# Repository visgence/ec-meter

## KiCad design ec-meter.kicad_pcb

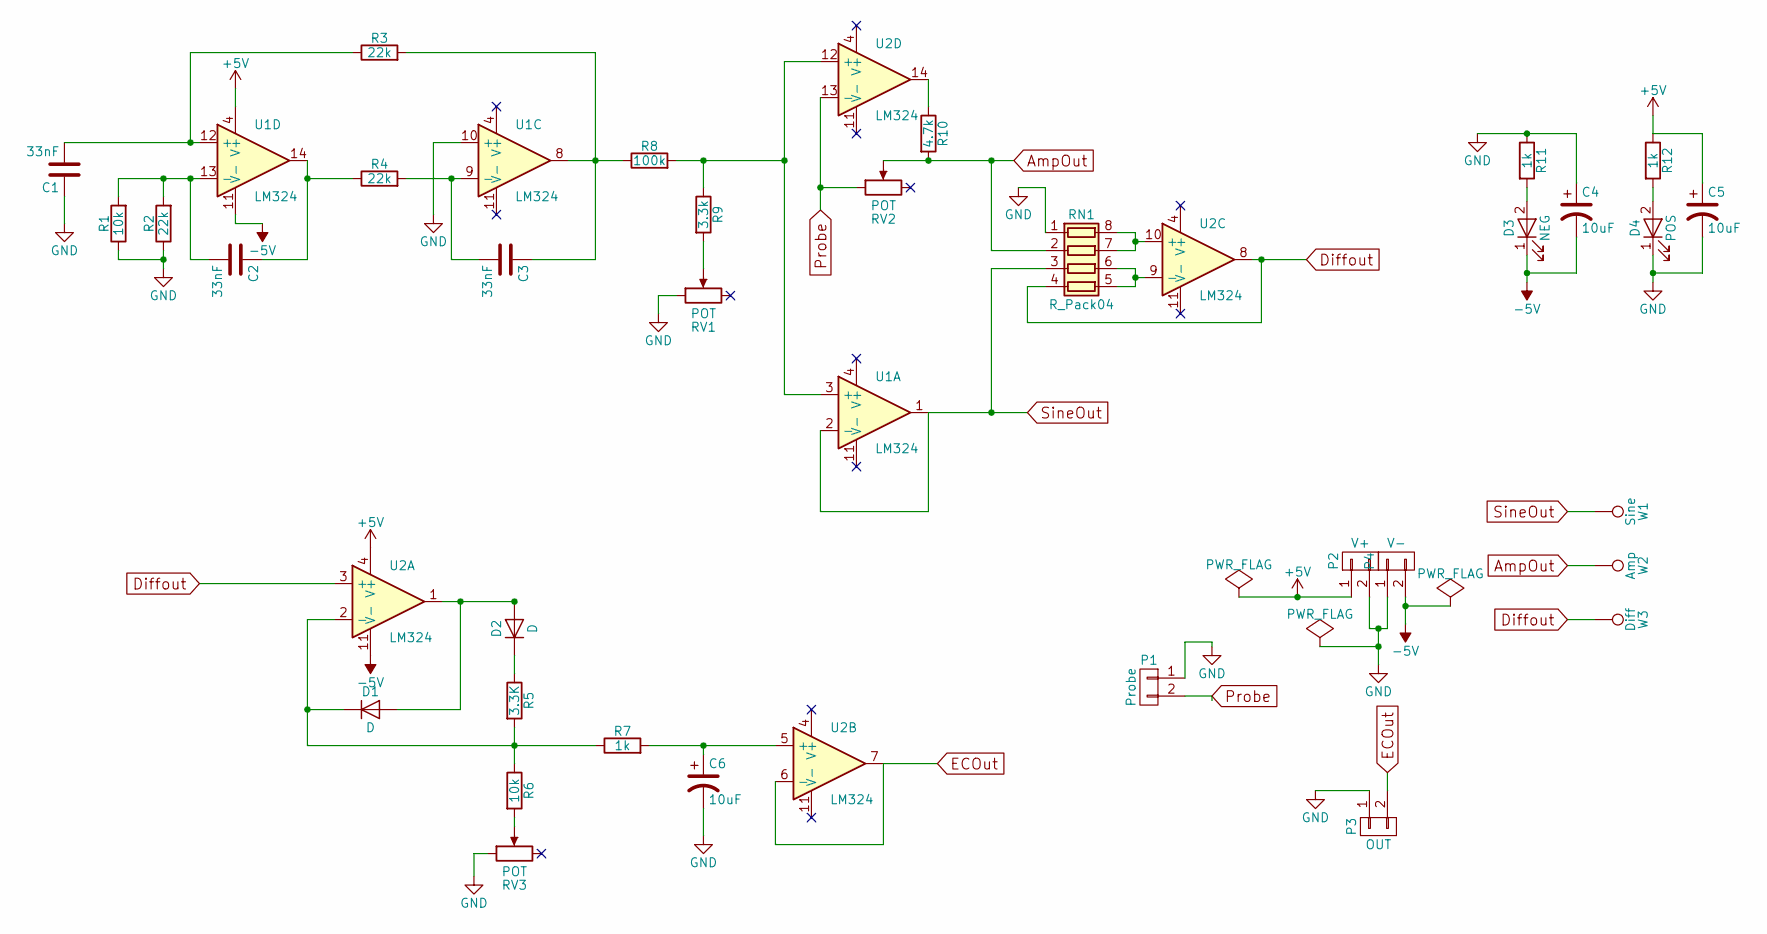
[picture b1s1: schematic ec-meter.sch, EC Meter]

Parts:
C1, C2, C3: 33nF; SM1206_VIS
C4, C5, C6: 10uF; SM1206POL_VIS
D1, D2: D; D_SOD-323
D3: NEG; LED_0603
D4: POS; LED_0603
P1: Probe; Term3.5-2
P2: V+; Term3.5-2
P3: OUT; Term3.5-2
P4: V-; Term3.5-2
R1, R6: 10k; SM0603_VIS
R2, R3, R4: 22k; SM0603_VIS
R5: 3.3K; SM0603_VIS
R7, R11, R12: 1k; SM0603_VIS
R8: 100k; SM0603_VIS
R9: 3.3k; SM0603_VIS
R10: 4.7k; SM0603_VIS
RN1: R_Pack04; RESARRAY-0612
RV1, RV2, RV3: POT; Var_resistor
U1, U2: LM324; SOIC-14_N
W1: Sine; Measurement_Point_Square-TH_Small
W2: Amp; Measurement_Point_Square-TH_Small
W3: Diff; Measurement_Point_Square-TH_Small

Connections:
+5V: C5.1, P2.1, R12.1, U1.4 (V+), U2.4 (V+)
-5V: C4.2, D3.1 (K), P4.2, U1.11 (V-), U2.11 (V-)
AmpOut: R10.2, RN1.2 (R2.1), RV2.2, W2.1
Diffout: RN1.4 (R4.1), U2.3 (+), U2.8, W3.1
ECOut: P3.2, U2.6 (-), U2.7
GND: C1.1, C4.1, C5.2, C6.2, D4.1 (K), P1.1, P2.2, P3.1, P4.1, R1.1, R2.1, R11.1, RN1.1 (R1.1), RV1.1, RV3.1, U1.10 (+)
unnamed: C1.2, R3.1, U1.12 (+)
unnamed: C2.1, R4.1, U1.14
unnamed: C2.2, R1.2, R2.2, U1.13 (-)
unnamed: C3.1, R3.2, R8.1, U1.8
unnamed: C3.2, R4.2, U1.9 (-)
unnamed: C6.1, R7.2, U2.5 (+)
unnamed: D1.1 (K), R5.2, R6.1, R7.1, U2.2 (-)
unnamed: D1.2 (A), D2.2 (A), U2.1
unnamed: D2.1 (K), R5.1
unnamed: D3.2 (A), R11.2
unnamed: D4.2 (A), R12.2
unnamed: R6.2, RV3.2
unnamed: R8.2, R9.1, U1.3 (+), U2.12 (+)
unnamed: R9.2, RV1.2
unnamed: R10.1, U2.14
unnamed: RN1.5 (R4.2), RN1.6 (R3.2), U2.9 (-)
unnamed: RN1.7 (R2.2), RN1.8 (R1.2), U2.10 (+)
Probe: P1.2, RV2.1, U2.13 (-)
SineOut: RN1.3 (R3.1), U1.1, U1.2 (-), W1.1

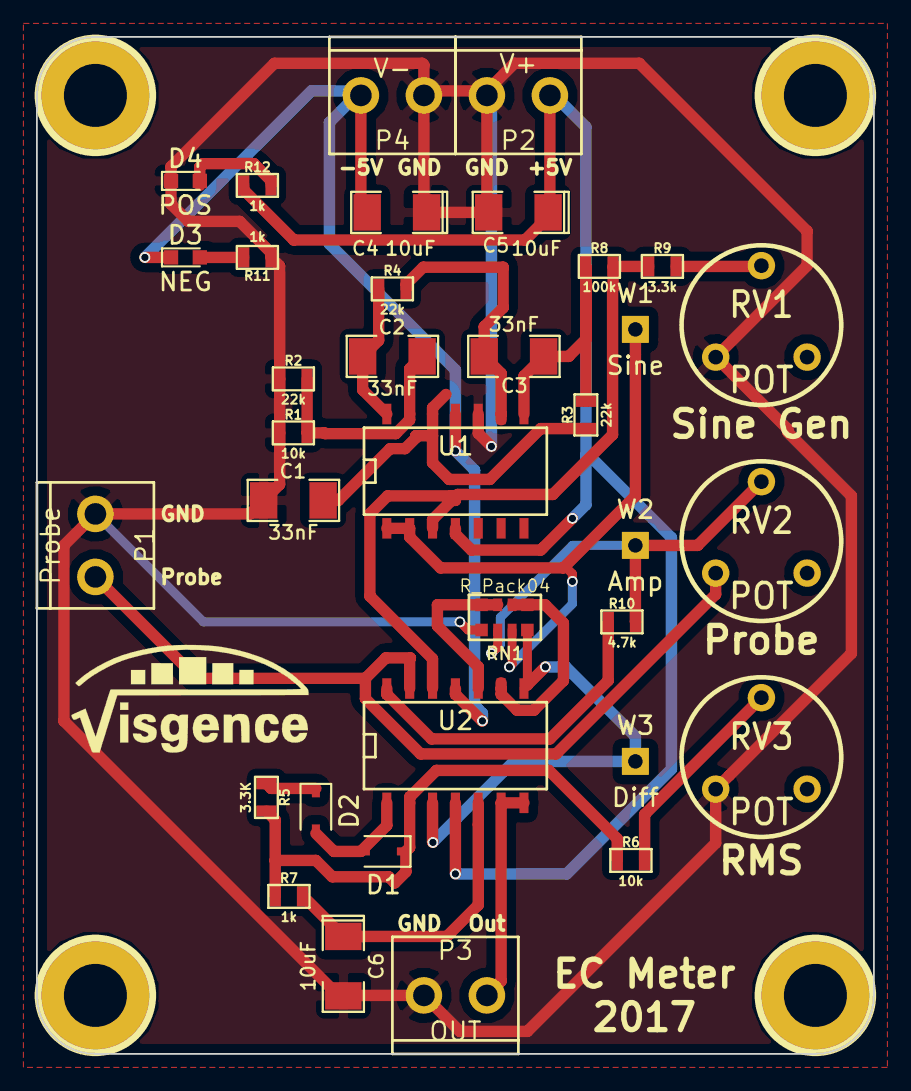
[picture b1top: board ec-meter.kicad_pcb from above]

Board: 2 copper layers, 46.5 x 56.5 mm, 39 parts (0 on the bottom side), 25 nets.

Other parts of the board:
h?: pin; 1pin_C
h?#2, h?#3, h?#4: pin; 1pin_C

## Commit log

2017-01-20 Start of new project
2017-01-20 Added sin wave gen
2017-01-22 Worked more on schematic
2017-01-22 Got schematic to pass DRC
2017-01-22 Mapped componets, fixed some references
2017-01-22 Started PCB, did some layout, fix some references
2017-01-22 Moved parts, rearranged opamps
2017-01-22 minor layout
2017-01-23 Did routing
2017-01-23 Fixed missing track
2017-01-23 Filled and added some labels
2017-01-23 final routing
2017-01-25 Changed direction of RV1
2017-01-25 Changed diode to reflowable one
2017-01-25 Rad gerber tool
